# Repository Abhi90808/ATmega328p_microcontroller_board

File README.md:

# ATmega328P Arduino Nano Clone — Custom MCU PCB Design

> A fully custom Arduino Nano-compatible microcontroller board designed from scratch in KiCad. Implements the ATmega328P with USB-to-serial programming, onboard 5V/3.3V regulation, and a compact 2-layer layout — production-ready and Gerber-verified.

---

## Overview

This project is a **ground-up recreation of the Arduino Nano form factor** using the ATmega328P microcontroller. Rather than using a pre-made module, the entire hardware stack was designed from scratch: oscillator circuit, decoupling strategy, USB-to-serial bridge for bootloader programming, voltage regulation, and pin breakout — all laid out in a compact 2-layer PCB.

This project demonstrates the ability to design real microcontroller hardware — the kind of work needed for custom embedded products where off-the-shelf dev boards aren't suitable.

---

## Specifications

| Parameter          | Value                              |
|--------------------|------------------------------------|
| MCU                | ATmega328P-AU (TQFP-32)            |
| Clock              | 16 MHz external crystal            |
| USB Interface      | CH340G USB-to-Serial bridge        |
| Supply Voltage     | 5V via USB                         |
| Onboard Regulation | AMS1117-3.3 (3.3V LDO)            |
| I/O Voltage        | 5V logic                           |
| GPIO Pins          | 22 (14 digital, 8 analog)          |
| Programming        | USB (bootloader) / ICSP header     |
| PCB Layers         | 2                                  |
| Board Status       | Design complete, DRC passed        |
| Tool               | KiCad                              |

---

## Design Highlights

### Full ATmega328P Bring-Up Circuit
Includes all essential support circuitry: 16 MHz crystal with load capacitors, AVCC filtering with a ferrite bead and bulk capacitor, 100nF decoupling caps on all VCC/GND pins, and a proper reset circuit with pull-up resistor and filter capacitor.

### USB-to-Serial Programming
The CH340G bridge handles USB communication and auto-reset for bootloader programming, matching the Arduino Nano behaviour exactly. DTR line connected through a 100nF capacitor to the MCU reset pin for reliable auto-reset during upload.

### Onboard 3.3V Regulation
AMS1117-3.3 LDO provides a clean 3.3V rail for sensors and peripherals that require it, with input and output decoupling capacitors for stability.

### Compact 2-Layer Layout
All components fit within a Nano-compatible footprint on a 2-layer board. Power and ground planes on bottom layer, signals routed cleanly on top. SMD components used throughout for compact placement.

### DRC Passed
Full design rule check with zero errors. Trace widths verified for current capacity, clearances verified for standard PCB fab tolerances.

---

## Repository Structure

```
project2-atmega328p-nano/
├── schematic/
│   └── atmega328p_nano.kicad_sch
├── pcb/
│   └── atmega328p_nano.kicad_pcb
├── gerbers/
│   ├── atmega328p_nano.GTL
│   ├── atmega328p_nano.GBL
│   ├── atmega328p_nano.GTO
│   ├── atmega328p_nano.GTS
│   ├── atmega328p_nano.GBS
│   └── atmega328p_nano.DRL
├── bom/
│   └── bom.csv
└── README.md
```

---

## Bill of Materials (Key Components)

| Ref      | Component           | Part Number       | Package    |
|----------|---------------------|-------------------|------------|
| U1       | Microcontroller     | ATmega328P-AU     | TQFP-32    |
| U2       | USB-Serial Bridge   | CH340G            | SOP-16     |
| U3       | 3.3V LDO Regulator  | AMS1117-3.3       | SOT-223    |
| Y1       | Crystal Oscillator  | 16 MHz            | HC-49S     |
| C1, C2   | Crystal Load Caps   | 22pF              | 0402       |
| C3–C10   | Decoupling Caps     | 100nF             | 0402       |
| R1       | Reset Pull-up       | 10kΩ              | 0402       |
| J1       | USB Connector       | Mini-USB Female   | SMD        |
| J2, J3   | Pin Headers         | 2.54mm, 15-pin    | Through-hole |
| J4       | ICSP Header         | 2×3, 2.54mm       | Through-hole |

---

## Schematic Sections

1. **Power input & regulation** — USB 5V in → AMS1117-3.3 → 3.3V rail
2. **USB-to-Serial** — CH340G with crystal, decoupling, and DTR auto-reset
3. **ATmega328P core** — MCU with crystal, decoupling, AVCC filter, reset
4. **I/O breakout** — all GPIO, analog, and power pins exposed on 2.54mm headers
5. **ICSP header** — for bootloader burning and direct ISP programming

---

## Skills Demonstrated

- ATmega328P hardware bring-up and support circuit design
- USB-to-serial bridge integration (CH340G)
- LDO regulator selection and decoupling strategy
- SMD component placement and 2-layer PCB routing
- ICSP and bootloader programming interface design
- KiCad DRC and Gerber export

---

## Project Status

| Stage            | Status       |
|------------------|--------------|
| Schematic        | ✅ Complete  |
| PCB Layout       | ✅ Complete  |
| DRC              | ✅ Passed    |
| Gerbers Exported | ✅ Ready     |
| Fabricated       | ⬜ Not yet   |
| Tested           | ⬜ Not yet   |

---

## About the Designer

Self-taught PCB designer specializing in KiCad — IoT, embedded systems, and industrial control boards.
Available for freelance PCB design work: schematic capture, layout, DRC review, and Gerber preparation.

🔗 GitHub: [Abhi90808]
📧 [kvabhishek908@gmail.com]

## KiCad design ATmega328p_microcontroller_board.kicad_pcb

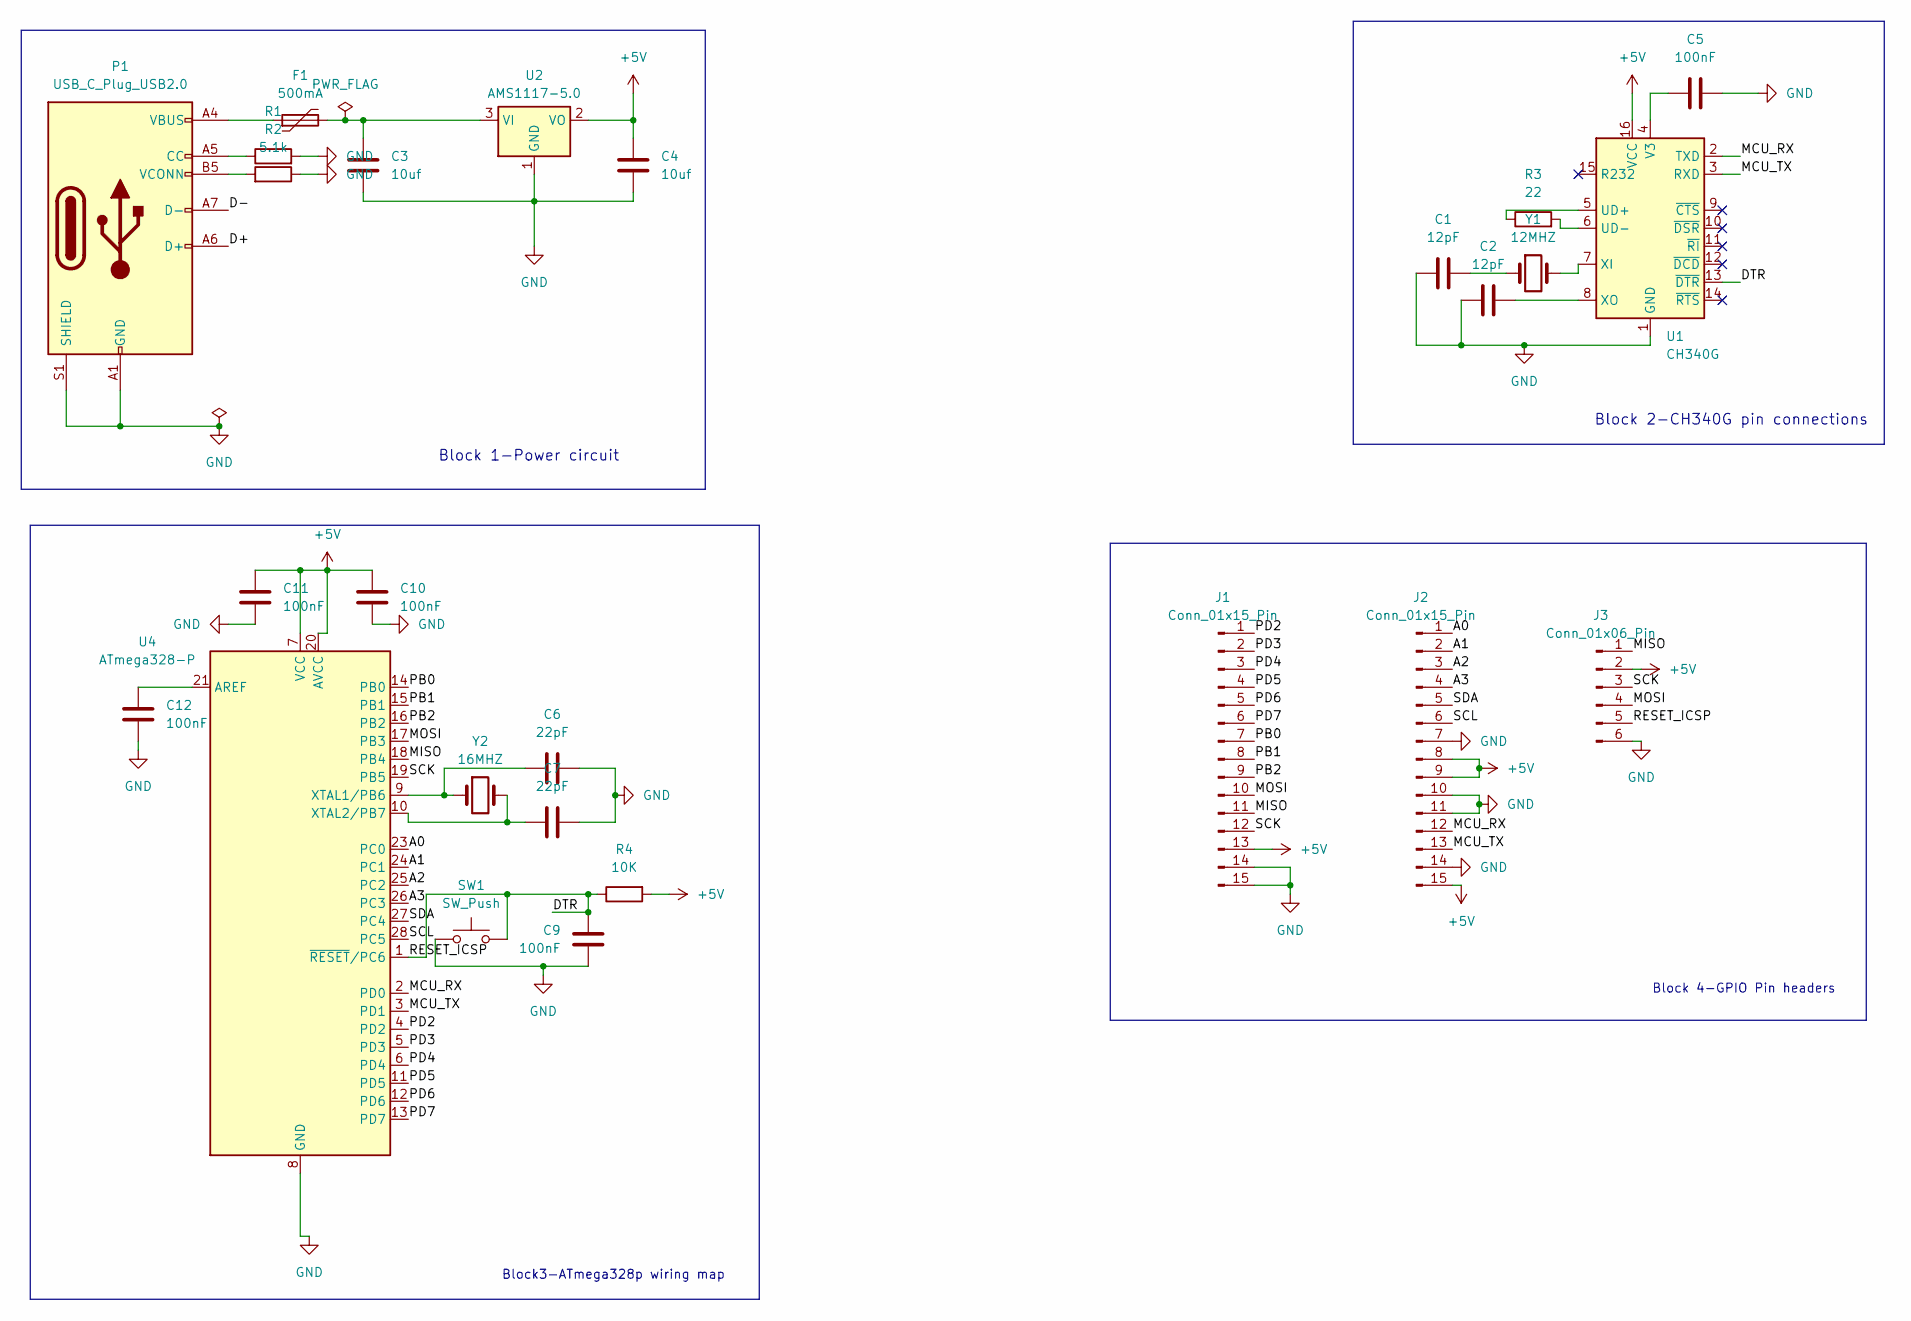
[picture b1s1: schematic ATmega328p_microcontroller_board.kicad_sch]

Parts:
C1, C2: 12pF; C_0402_1005Metric
C3, C4: 10uf; C_0805_2012Metric
C5, C9, C10, C11, C12: 100nF; C_0402_1005Metric
C6, C7: 22pF; C_0402_1005Metric
F1: 500mA; Fuse_0805_2012Metric
J1, J2: Conn_01x15_Pin; PinHeader_1x15_P2.54mm_Vertical
J3: Conn_01x06_Pin; PinHeader_2x03_P2.54mm_Vertical
P1: USB_C_Plug_USB2.0; USB_C_Receptacle_HRO_TYPE-C-31-M-12
R1: 5.1K; R_0402_1005Metric
R2: 5.1k; R_0402_1005Metric
R3: 22; R_0402_1005Metric
R4: 10K; R_0402_1005Metric
SW1: SW_Push; SW_SPST_B3U-1000P
U1: CH340G; SOIC-16_3.9x9.9mm_P1.27mm
U2: AMS1117-5.0; SOT-223-3_TabPin2
U4: ATmega328-P; TQFP-32_7x7mm_P0.8mm
Y1: 12MHZ; Crystal_SMD_3225-4Pin_3.2x2.5mm
Y2: 16MHZ; Crystal_SMD_3225-4Pin_3.2x2.5mm

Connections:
+5V: C4.1, C10.2, C11.2, J1.13, J2.8, J2.9, J2.15, J3.2, R4.2, U1.16 (VCC), U2.2 (VO), U4.7 (VCC), U4.20 (AVCC)
/A0: J2.1, U4.23 (PC0)
/A1: J2.2, U4.24 (PC1)
/A2: J2.3, U4.25 (PC2)
/A3: J2.4, U4.26 (PC3)
/D+: P1.A6 (D+)
/D-: P1.A7 (D-)
/DTR: C9.1, J3.5, R4.1, SW1.1, U1.13 (~DTR), U4.1 (~RESET/PC6)
/MCU_RX: J2.12, U1.2 (TXD), U4.2 (PD0)
/MCU_TX: J2.13, U1.3 (RXD), U4.3 (PD1)
/MISO: J1.11, J3.1, U4.18 (PB4)
/MOSI: J1.10, J3.4, U4.17 (PB3)
/PB0: J1.7, U4.14 (PB0)
/PB1: J1.8, U4.15 (PB1)
/PB2: J1.9, U4.16 (PB2)
/PD2: J1.1, U4.4 (PD2)
/PD3: J1.2, U4.5 (PD3)
/PD4: J1.3, U4.6 (PD4)
/PD5: J1.4, U4.11 (PD5)
/PD6: J1.5, U4.12 (PD6)
/PD7: J1.6, U4.13 (PD7)
/SCK: J1.12, J3.3, U4.19 (PB5)
/SCL: J2.6, U4.28 (PC5)
/SDA: J2.5, U4.27 (PC4)
GND: C1.2, C2.1, C3.2, C4.2, C5.2, C6.2, C7.2, C9.2, C10.1, C11.1, C12.1, J1.14, J1.15, J2.7, J2.10, J2.11, J2.14, J3.6, P1.A1 (GND), P1.A12 (GND), P1.B1 (GND), P1.B12 (GND), P1.S1 (SHIELD), R1.2, R2.1, SW1.2, U1.1 (GND), U2.1 (GND), U4.8 (GND), U4.22 (GND)
unnamed: C1.1, Y1.1
unnamed: F1.1, P1.A4 (VBUS), P1.A9 (VBUS), P1.B4 (VBUS), P1.B9 (VBUS)
unnamed: P1.A5 (CC), R1.1
unnamed: P1.B5 (VCONN), R2.2
unnamed: R3.1, U1.5 (UD+)
unnamed: R3.2, U1.6 (UD-)
unnamed: C5.1, U1.4 (V3)
unnamed: U1.7 (XI), Y1.2
unnamed: C2.2, U1.8 (XO)
unnamed: C3.1, F1.2, U2.3 (VI)
unnamed: C12.2, U4.21 (AREF)
unnamed: C6.1, U4.9 (XTAL1/PB6), Y2.1
unnamed: C7.1, U4.10 (XTAL2/PB7), Y2.2

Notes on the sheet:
Block 4-GPIO Pin headers
Block 1-Power circuit
Block 2-CH340G pin connections
Block3-ATmega328p wiring map

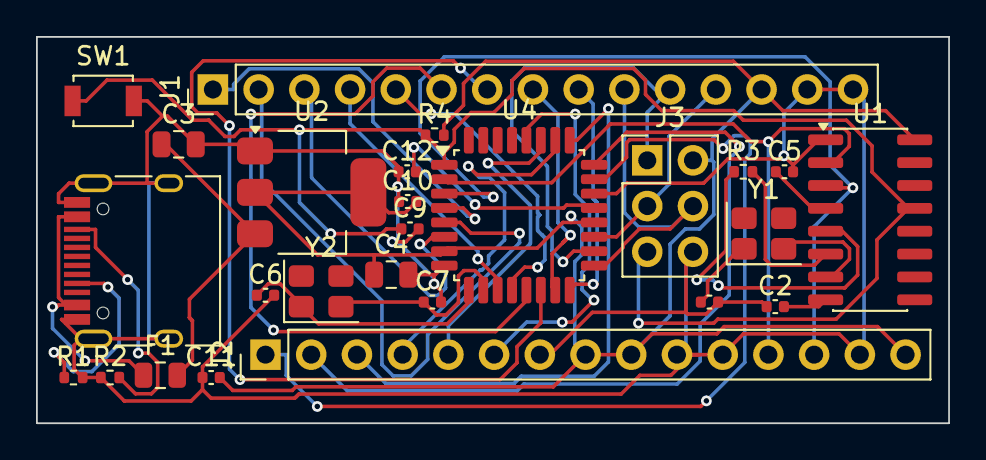
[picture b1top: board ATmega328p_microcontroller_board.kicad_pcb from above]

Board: 2 copper layers, 50.7 x 21.5 mm, 26 parts (0 on the bottom side), 36 nets.

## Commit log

2026-04-14 Add files via upload
    Add PCB Design Files
